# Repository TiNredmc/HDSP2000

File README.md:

# HDSP2000
HDSP200x series with ATtiny84 microcontroller

# Link for order or donwload PCB(s)
https://oshpark.com/shared_projects/43QgMIs4

# Credit for original code 
http://bitsnbikes.blogspot.com/2010/05/hdsp-2000lp-arduino.html

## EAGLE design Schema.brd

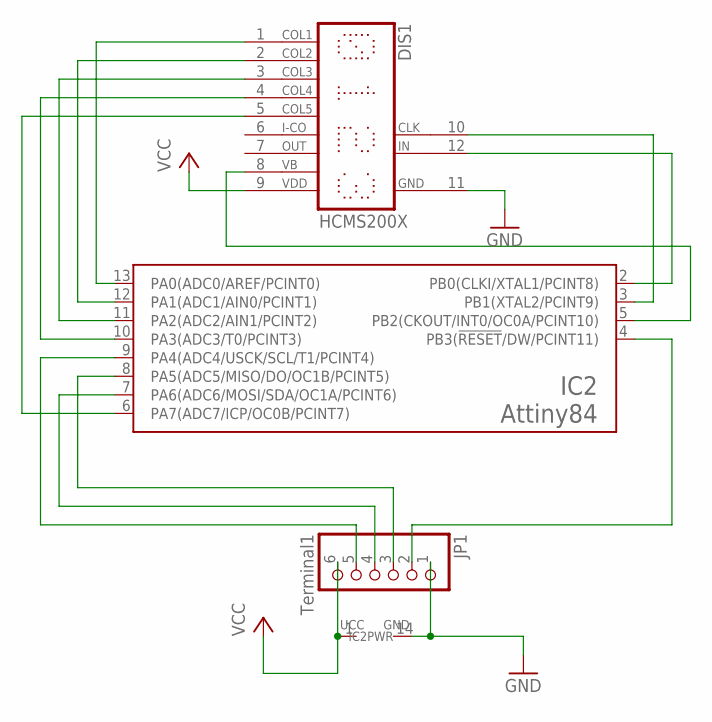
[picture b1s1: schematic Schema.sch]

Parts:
DIS1: HCMS200X
IC2: Attiny84; DIL14
JP1: Terminal1; 1X06

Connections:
GND: DIS1.11 (GND), IC2.14 (GND), JP1.1
unnamed: DIS1.1 (COL1), IC2.13 (PA0(ADC0/AREF/PCINT0))
unnamed: DIS1.2 (COL2), IC2.12 (PA1(ADC1/AIN0/PCINT1))
unnamed: DIS1.3 (COL3), IC2.11 (PA2(ADC2/AIN1/PCINT2))
unnamed: DIS1.4 (COL4), IC2.10 (PA3(ADC3/T0/PCINT3))
unnamed: DIS1.5 (COL5), IC2.6 (PA7(ADC7/ICP/OC0B/PCINT7))
unnamed: DIS1.12 (IN), IC2.2 (PB0(CLKI/XTAL1/PCINT8))
unnamed: DIS1.10 (CLK), IC2.3 (PB1(XTAL2/PCINT9))
unnamed: DIS1.8 (VB), IC2.5 (PB2(CKOUT/INT0/OC0A/PCINT10))
unnamed: IC2.9 (PA4(ADC4/USCK/SCL/T1/PCINT4)), JP1.5
unnamed: IC2.4 (PB3(!RESET!/DW/PCINT11)), JP1.2
unnamed: IC2.7 (PA6(ADC6/MOSI/SDA/OC1A/PCINT6)), JP1.4
unnamed: IC2.8 (PA5(ADC5/MISO/DO/OC1B/PCINT5)), JP1.3
VCC: DIS1.9 (VDD), IC2.1 (UCC), JP1.6

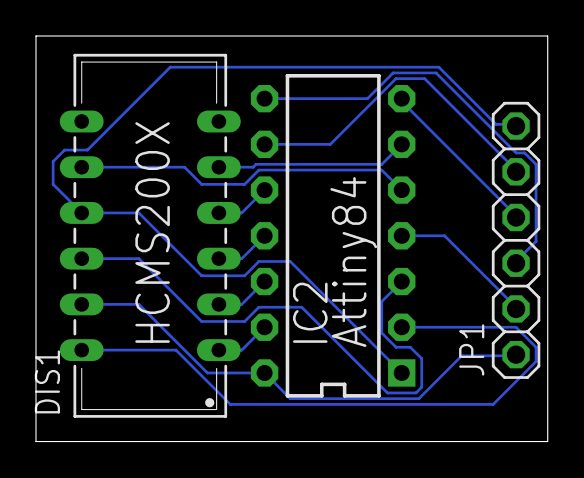
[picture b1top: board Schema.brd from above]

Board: 2 copper layers, 28.4 x 22.5 mm, 3 parts (0 on the bottom side), 14 nets.

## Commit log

2018-07-13 The ATtiny84 dip PCB
2018-07-13 Preview images form OSHpark
2018-07-13 added the pcb order link from oshpark
2018-07-14 credit to the original code owner
2018-07-14 The MODDED code
2018-07-15 The code for attiny84
    all credit will put in the readme.md
2018-07-15 added the credit to original code
